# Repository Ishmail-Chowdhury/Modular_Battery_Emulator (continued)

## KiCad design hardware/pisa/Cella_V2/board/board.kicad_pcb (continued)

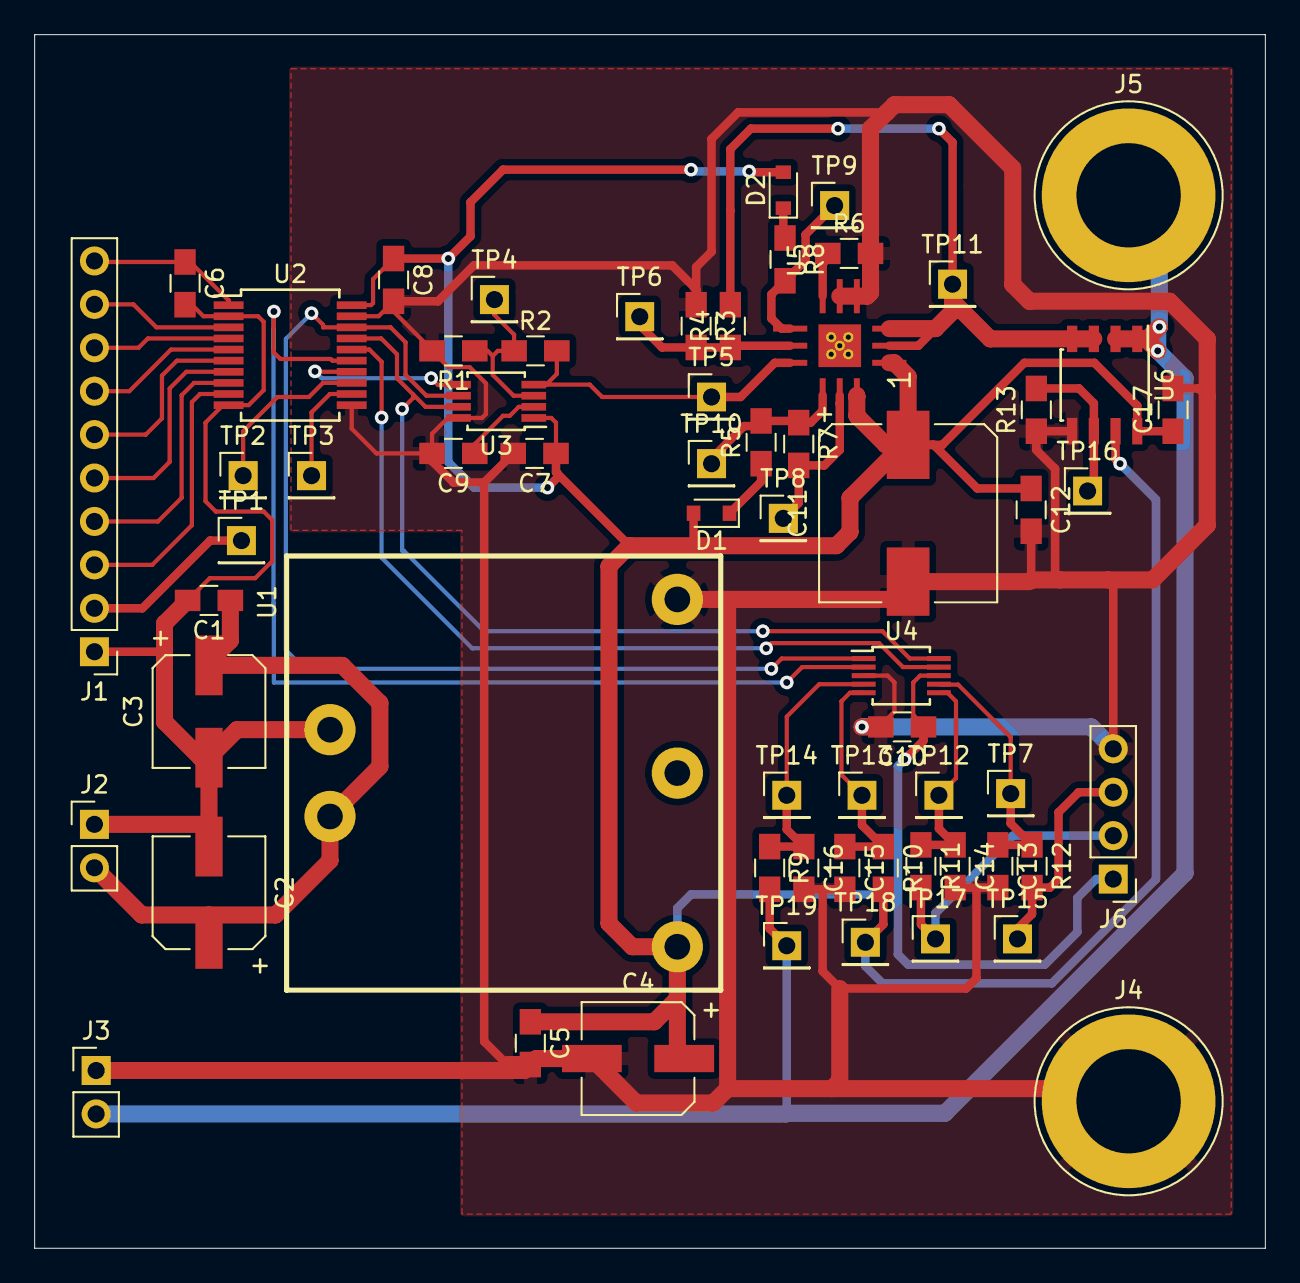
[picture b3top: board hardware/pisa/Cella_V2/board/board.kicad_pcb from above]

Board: 2 copper layers, 72.0 x 71.0 mm, 63 parts (0 on the bottom side), 40 nets.

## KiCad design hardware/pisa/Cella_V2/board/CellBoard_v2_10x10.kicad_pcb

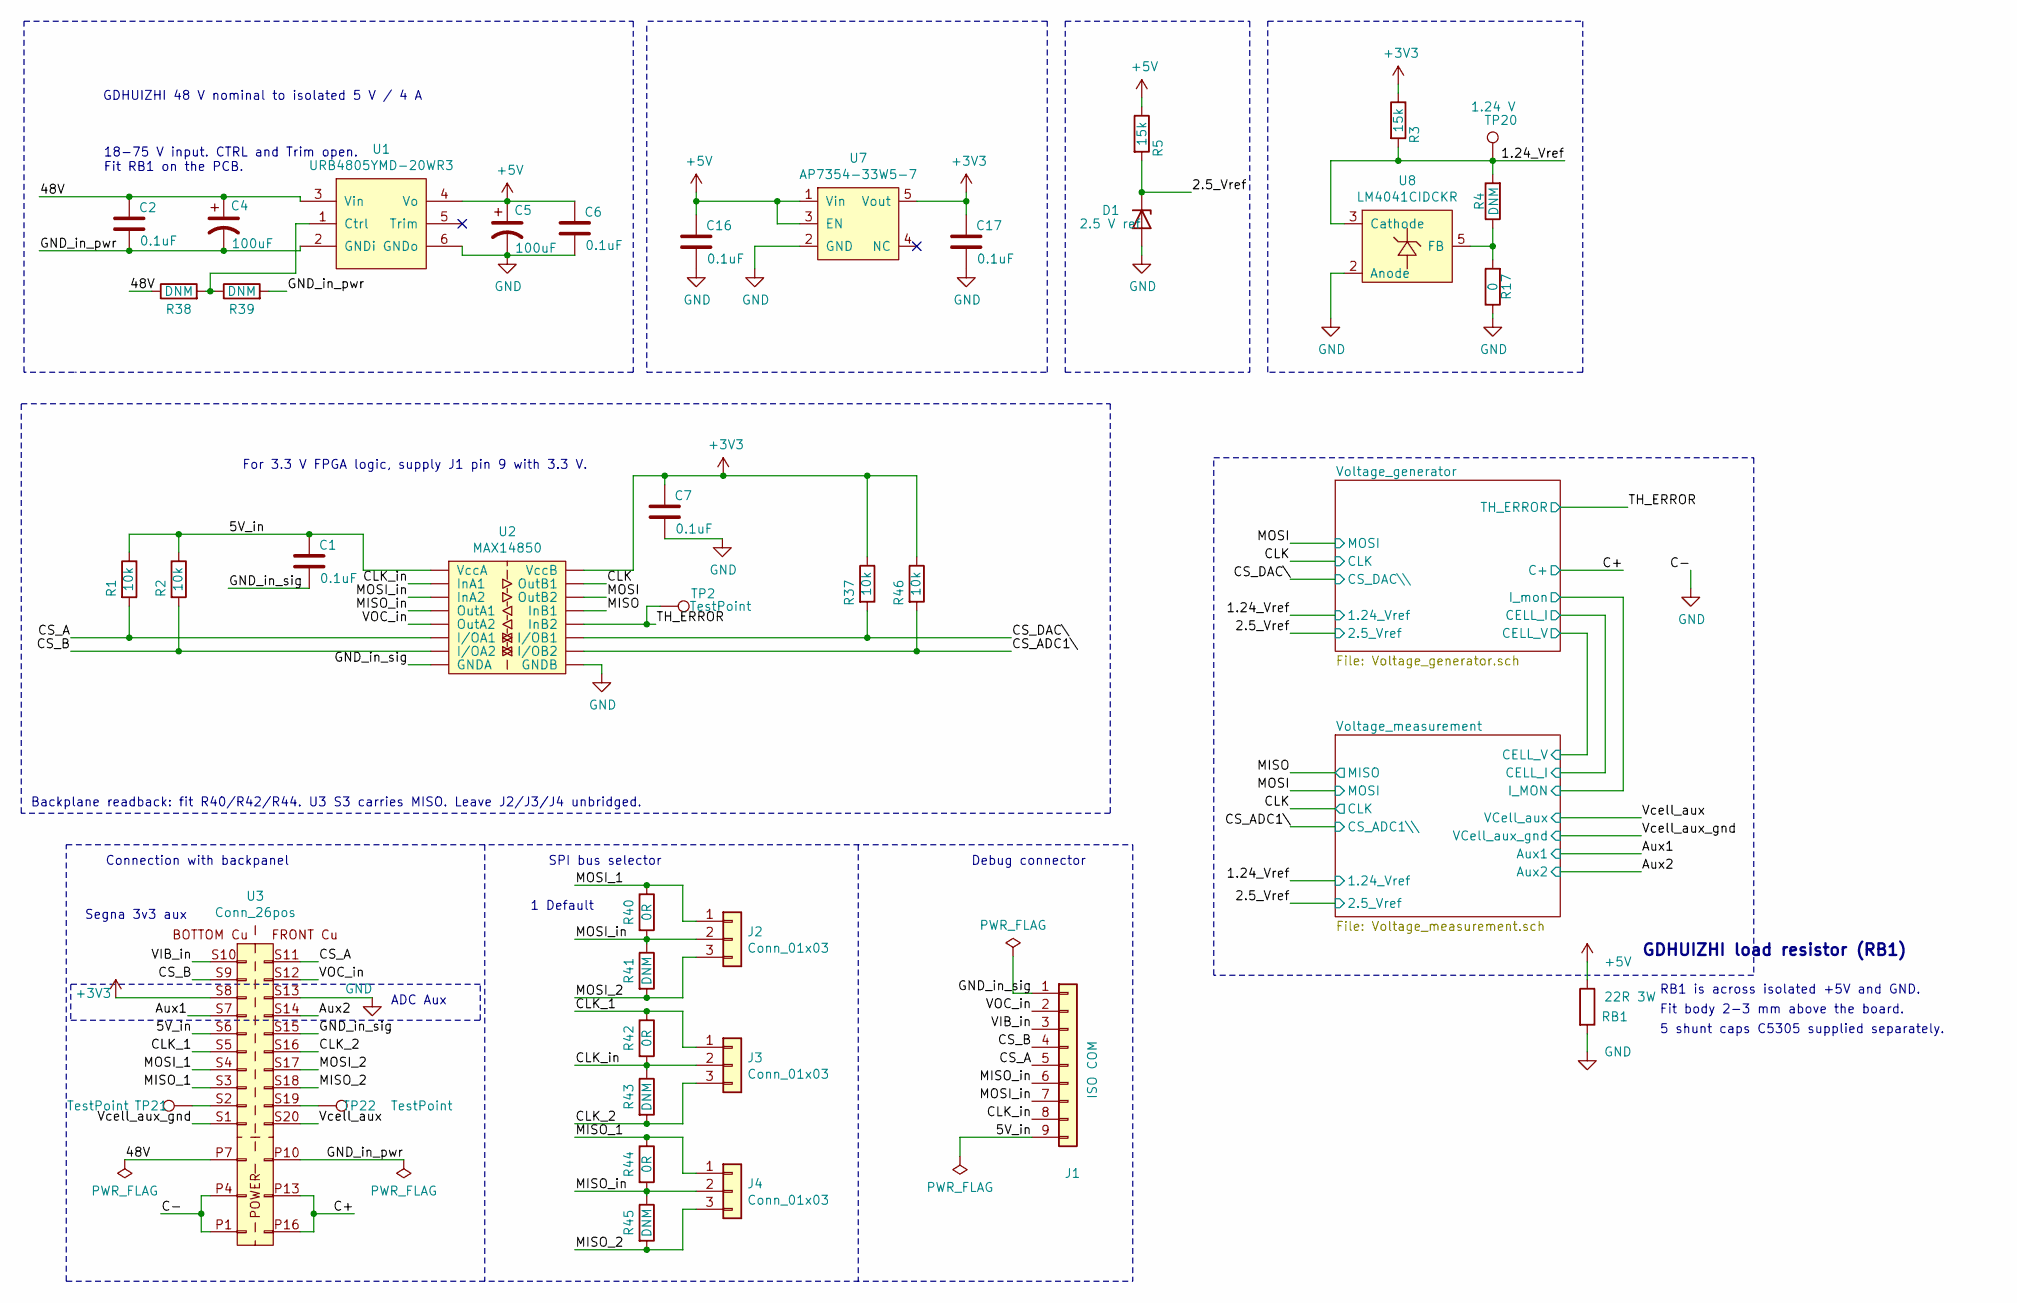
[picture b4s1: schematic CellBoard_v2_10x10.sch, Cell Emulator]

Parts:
C1, C2, C6, C7, C16, C17: 0.1uF; C_0805_2012Metric_Pad1.18x1.45mm_HandSolder; JLCPCB C28233
C4, C5: 100uF; CP_Radial_D10.0mm_P5.00mm; JLCPCB C330940
D1: 2.5 V ref; SOT-23; JLCPCB C2157047
J1: ISO COM; PinHeader_1x09_P2.54mm_Vertical; JLCPCB C2337
J2, J3, J4: Conn_01x03; PinHeader_1x03_P2.54mm_Vertical; JLCPCB C2337
R1, R2, R37, R46: 10k; R_0805_2012Metric_Pad1.20x1.40mm_HandSolder; JLCPCB C110775
R3, R5: 15k; R_0805_2012Metric_Pad1.20x1.40mm_HandSolder; JLCPCB C17475
R4: DNM; R_0805_2012Metric_Pad1.20x1.40mm_HandSolder; Digikey PN RMCF0805ZT0R00CT-ND
R17: 0; R_0805_2012Metric_Pad1.20x1.40mm_HandSolder; JLCPCB C17477
R38, R39: DNM; R_0603_1608Metric_Pad0.98x0.95mm_HandSolder
R40, R42, R44: 0R; R_0402_1005Metric_Pad0.72x0.64mm_HandSolder; JLCPCB C106231
R41, R43, R45: DNM; R_0402_1005Metric_Pad0.72x0.64mm_HandSolder; Digikey PN RMCF0805ZT0R00CT-ND
RB1: 22R 3W; R_Axial_DIN0516_L15.5mm_D5.0mm_P20.32mm_Horizontal; JLCPCB C122827
TP2, TP21, TP22: TestPoint; PinHeader_1x01_P2.54mm_Vertical
TP20: 1.24 V; PinHeader_1x01_P2.54mm_Vertical
U1: URB4805YMD-20WR3; JLCPCB C55020094
U2: MAX14850; SOIC-16_3.9x9.9mm_P1.27mm; JLCPCB C143356
U3: Conn_26pos; Conn_26pos_Board; Digikey PN A107666-ND (Header)
U7: AP7354-33W5-7; TSOT-23-5_HandSoldering; JLCPCB C460386
U8: LM4041CIDCKR; JLCPCB C2156783

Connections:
+3V3: C7.1, C17.1, R3.1, R37.1, R46.1, U2.16 (VccB), U3.S8, U7.5 (Vout); also elsewhere on the board
+5V: C5.1, C6.1, C16.1, R5.1, RB1.1, U1.4 (Vo), U7.1 (Vin), U7.3 (EN); also elsewhere on the board
/1.24_Vref: R3.2, R4.2, TP20.1, U8.3 (Cathode); also elsewhere on the board
/2.5_Vref: D1.1 (K), R5.2; also elsewhere on the board
/5V_in: C1.1, J1.9, R1.1, R2.1, U2.1 (VccA), U3.S6
/48V: C2.1, C4.1, R38.1, U1.3 (Vin), U3.P7
/Aux1: U3.S7; also elsewhere on the board
/Aux2: U3.S14; also elsewhere on the board
/C+: U3.P13, U3.P16; also elsewhere on the board
/CLK: U2.15 (OutB1); also elsewhere on the board
/CLK_1: J3.1, R42.1, U3.S5
/CLK_2: J3.3, R43.2, U3.S16
/CLK_in: J1.8, J3.2, R42.2, R43.1, U2.2 (InA1)
/CS_A: J1.5, R1.2, U2.6 (I/OA1), U3.S11
/CS_ADC1\: R46.2, U2.10 (I/OB2); also elsewhere on the board
/CS_B: J1.4, R2.2, U2.7 (I/OA2), U3.S9
/CS_DAC\: R37.2, U2.11 (I/OB1); also elsewhere on the board
/GND_in_pwr: C2.2, C4.2, R39.2, U1.2 (GNDi), U3.P10
/GND_in_sig: C1.2, J1.1, U2.8 (GNDA), U3.S15
/MISO: U2.13 (InB1); also elsewhere on the board
/MISO_1: J4.1, R44.1, U3.S3
/MISO_2: J4.3, R45.2, U3.S18
/MISO_in: J1.6, J4.2, R44.2, R45.1, U2.4 (OutA1)
/MOSI: U2.14 (OutB2); also elsewhere on the board
/MOSI_1: J2.1, R40.1, U3.S4
/MOSI_2: J2.3, R41.2, U3.S17
/MOSI_in: J1.7, J2.2, R40.2, R41.1, U2.3 (InA2)
/TH_ERROR: TP2.1, U2.12 (InB2); also elsewhere on the board
/VIB_in: J1.3, U3.S10
/VOC_in: J1.2, U2.5 (OutA2), U3.S12
/Vcell_aux: U3.S20; also elsewhere on the board
/Vcell_aux_gnd: U3.S1; also elsewhere on the board
GND: C5.2, C6.2, C7.2, C16.2, C17.2, D1.2 (A), R17.1, RB1.2, U1.6 (GNDo), U2.9 (GNDB), U3.P1, U3.P4, U3.S13, U7.2 (GND), U8.2 (Anode); also elsewhere on the board
unnamed: R4.1, R17.2, U8.5 (FB)
unnamed: R38.2, R39.1, U1.1 (Ctrl)
unnamed: TP21.1, U3.S2
unnamed: TP22.1, U3.S19

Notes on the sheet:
18-75 V input. CTRL and Trim open. Fit RB1 on the PCB.
Connection with backpanel
For 3.3 V FPGA logic, supply J1 pin 9 with 3.3 V.
GDHUIZHI 48 V nominal to isolated 5 V / 4 A
SPI bus selector
Debug connector
1 Default
Segna 3v3 aux
ADC Aux
GDHUIZHI load resistor (RB1)
RB1 is across isolated +5V and GND.
Fit body 2-3 mm above the board.
5 shunt caps C5305 supplied separately.
Backplane readback: fit R40/R42/R44. U3 S3 carries MISO. Leave J2/J3/J4 unbridged.

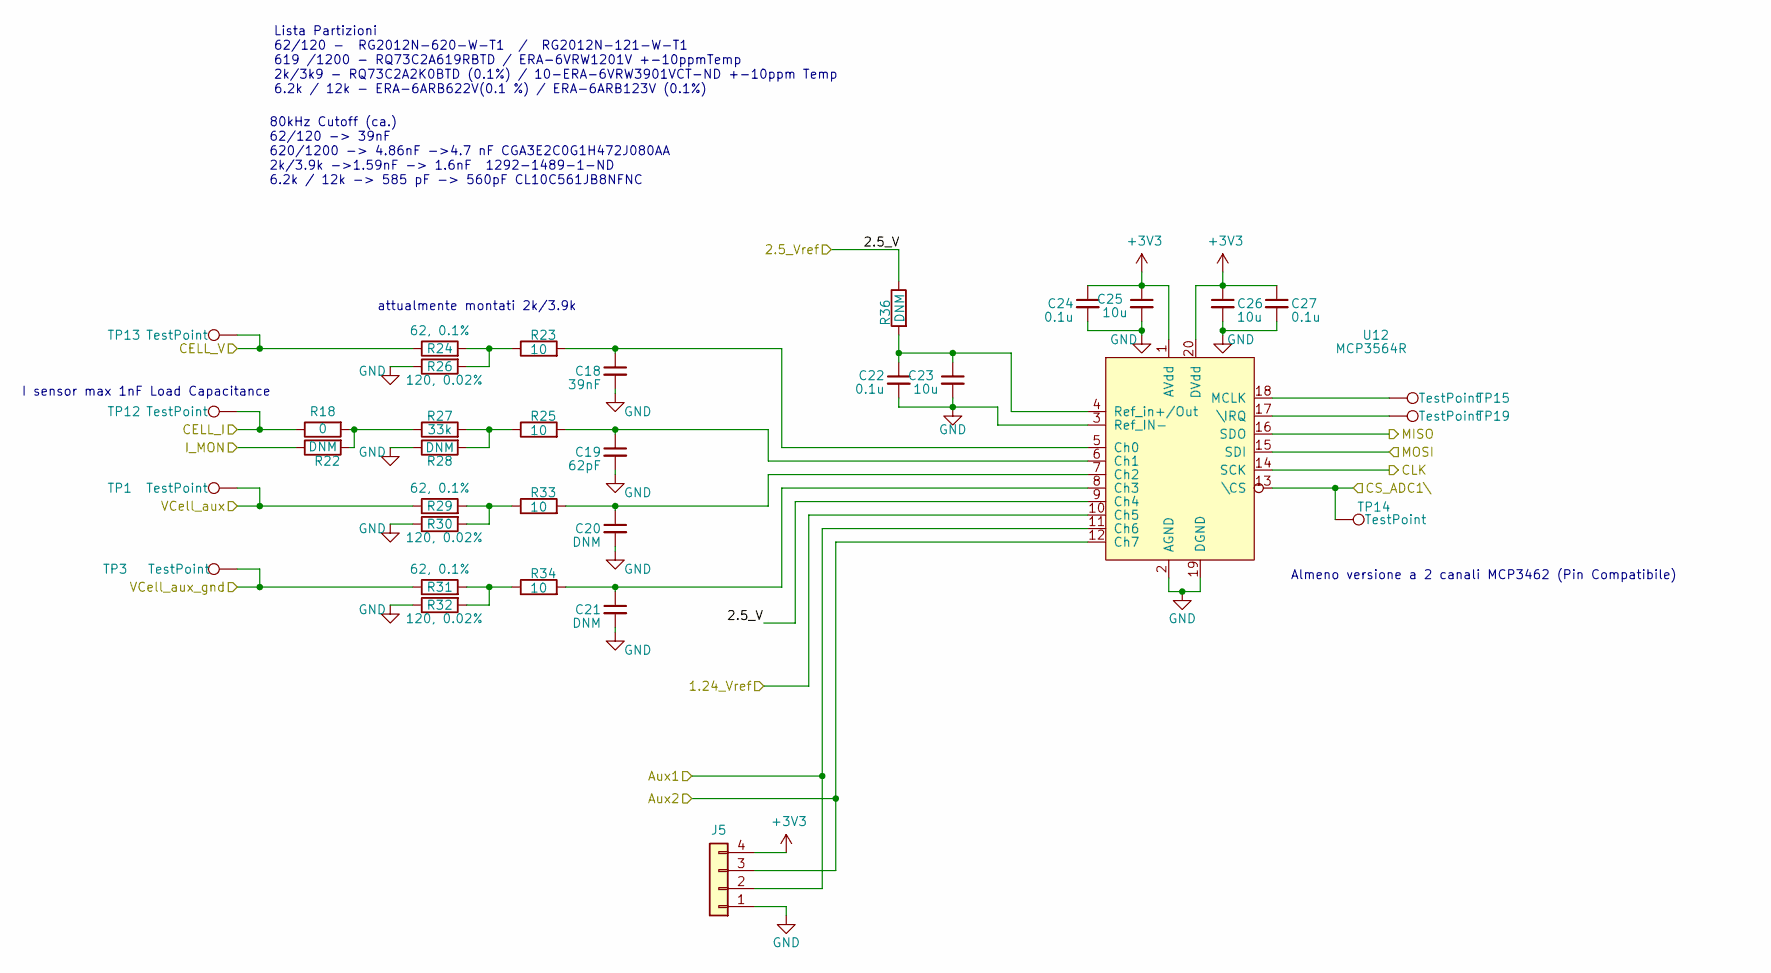
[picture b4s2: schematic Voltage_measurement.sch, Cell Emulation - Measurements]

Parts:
C18: 39nF; C_0603_1608Metric_Pad1.08x0.95mm_HandSolder; JLCPCB C318636
C19: 62pF; C_0603_1608Metric_Pad1.08x0.95mm_HandSolder; JLCPCB C519495
C20, C21: DNM; C_0603_1608Metric_Pad1.08x0.95mm_HandSolder; Digikey PN 1276-2057-1-ND
C22, C24, C27: 0.1u; C_0603_1608Metric_Pad1.08x0.95mm_HandSolder; JLCPCB C1591
C23, C25, C26: 10u; C_0805_2012Metric_Pad1.18x1.45mm_HandSolder; JLCPCB C3039694
J5: Conn_01x04-Connector_Generic; PinHeader_1x04_P2.54mm_Vertical; JLCPCB C2337
R18: 0; R_0805_2012Metric_Pad1.20x1.40mm_HandSolder; JLCPCB C17477
R22, R36: DNM; R_0805_2012Metric_Pad1.20x1.40mm_HandSolder; Digikey PN RMCF0805ZT0R00CT-ND
R23, R25, R33, R34: 10; R_0603_1608Metric_Pad0.98x0.95mm_HandSolder; JLCPCB C3029194
R24, R29, R31: 62, 0.1%; R_0805_2012Metric_Pad1.20x1.40mm_HandSolder; JLCPCB C351555
R26, R30, R32: 120, 0.02%; R_0805_2012Metric_Pad1.20x1.40mm_HandSolder; JLCPCB C19706317
R27: 33k; R_0805_2012Metric_Pad1.20x1.40mm_HandSolder; JLCPCB C17633
R28: DNM; R_0805_2012Metric_Pad1.20x1.40mm_HandSolder
TP1, TP3, TP12, TP13, TP14, TP15, TP19: TestPoint; PinHeader_1x01_P2.54mm_Vertical
U12: MCP3564R; TSSOP-20_4.4x6.5mm_P0.65mm; JLCPCB C5227404

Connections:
+3V3: C24.1, C25.1, C26.1, C27.1, J5.4, U12.1 (AVdd), U12.20 (DVdd); also elsewhere on the board
/1.24_Vref: U12.10 (Ch5); also elsewhere on the board
/2.5_Vref: R36.1, U12.9 (Ch4); also elsewhere on the board
/Aux1: J5.2, U12.11 (Ch6); also elsewhere on the board
/Aux2: J5.3, U12.12 (Ch7); also elsewhere on the board
/C+: R24.1, TP13.1; also elsewhere on the board
/CLK: U12.14 (SCK); also elsewhere on the board
/CS_ADC1\: TP14.1, U12.13 (\CS); also elsewhere on the board
/MISO: U12.16 (SDO); also elsewhere on the board
/MOSI: U12.15 (SDI); also elsewhere on the board
/Vcell_aux: R29.1, TP1.1; also elsewhere on the board
/Vcell_aux_gnd: R31.1, TP3.1; also elsewhere on the board
/Voltage_generator/CELL_I: R18.1, TP12.1; also elsewhere on the board
/Voltage_measurement/I_MON: R22.1; also elsewhere on the board
GND: C18.2, C19.2, C20.2, C21.2, C22.2, C23.2, C24.2, C25.2, C26.2, C27.2, J5.1, R26.1, R28.1, R30.1, R32.1, U12.2 (AGND), U12.3 (Ref_IN-), U12.19 (DGND); also elsewhere on the board
unnamed: C18.1, R23.2, U12.5 (Ch0)
unnamed: C19.1, R25.2, U12.6 (Ch1)
unnamed: C20.1, R33.2, U12.7 (Ch2)
unnamed: C21.1, R34.2, U12.8 (Ch3)
unnamed: C22.1, C23.1, R36.2, U12.4 (Ref_in+/Out)
unnamed: R18.2, R22.2, R27.1
unnamed: R23.1, R24.2, R26.2
unnamed: R25.1, R27.2, R28.2
unnamed: R29.2, R30.2, R33.1
unnamed: R31.2, R32.2, R34.1
unnamed: TP15.1, U12.18 (MCLK)
unnamed: TP19.1, U12.17 (\IRQ)

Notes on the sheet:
Lista Partizioni 62/120 - RG2012N-620-W-T1 / RG2012N-121-W-T1 619 /1200 - RQ73C2A619RBTD / ERA-6VRW1201V +-10ppmTemp 2k/3k9 - RQ73C2A2K0BTD (0.1%) / 10-ERA-6VRW3901VCT-ND +-10ppm Temp 6.2k / 12k - ERA-6ARB622V(0.1 %) / ERA-6ARB123V (0.1%)
I sensor max 1nF Load Capacitance
80kHz Cutoff (ca.) 62/120 -> 39nF 620/1200 -> 4.86nF ->4.7 nF CGA3E2C0G1H472J080AA 2k/3.9k ->1.59nF -> 1.6nF 1292-1489-1-ND 6.2k / 12k -> 585 pF -> 560pF CL10C561JB8NFNC
Almeno versione a 2 canali MCP3462 (Pin Compatibile)
attualmente montati 2k/3.9k

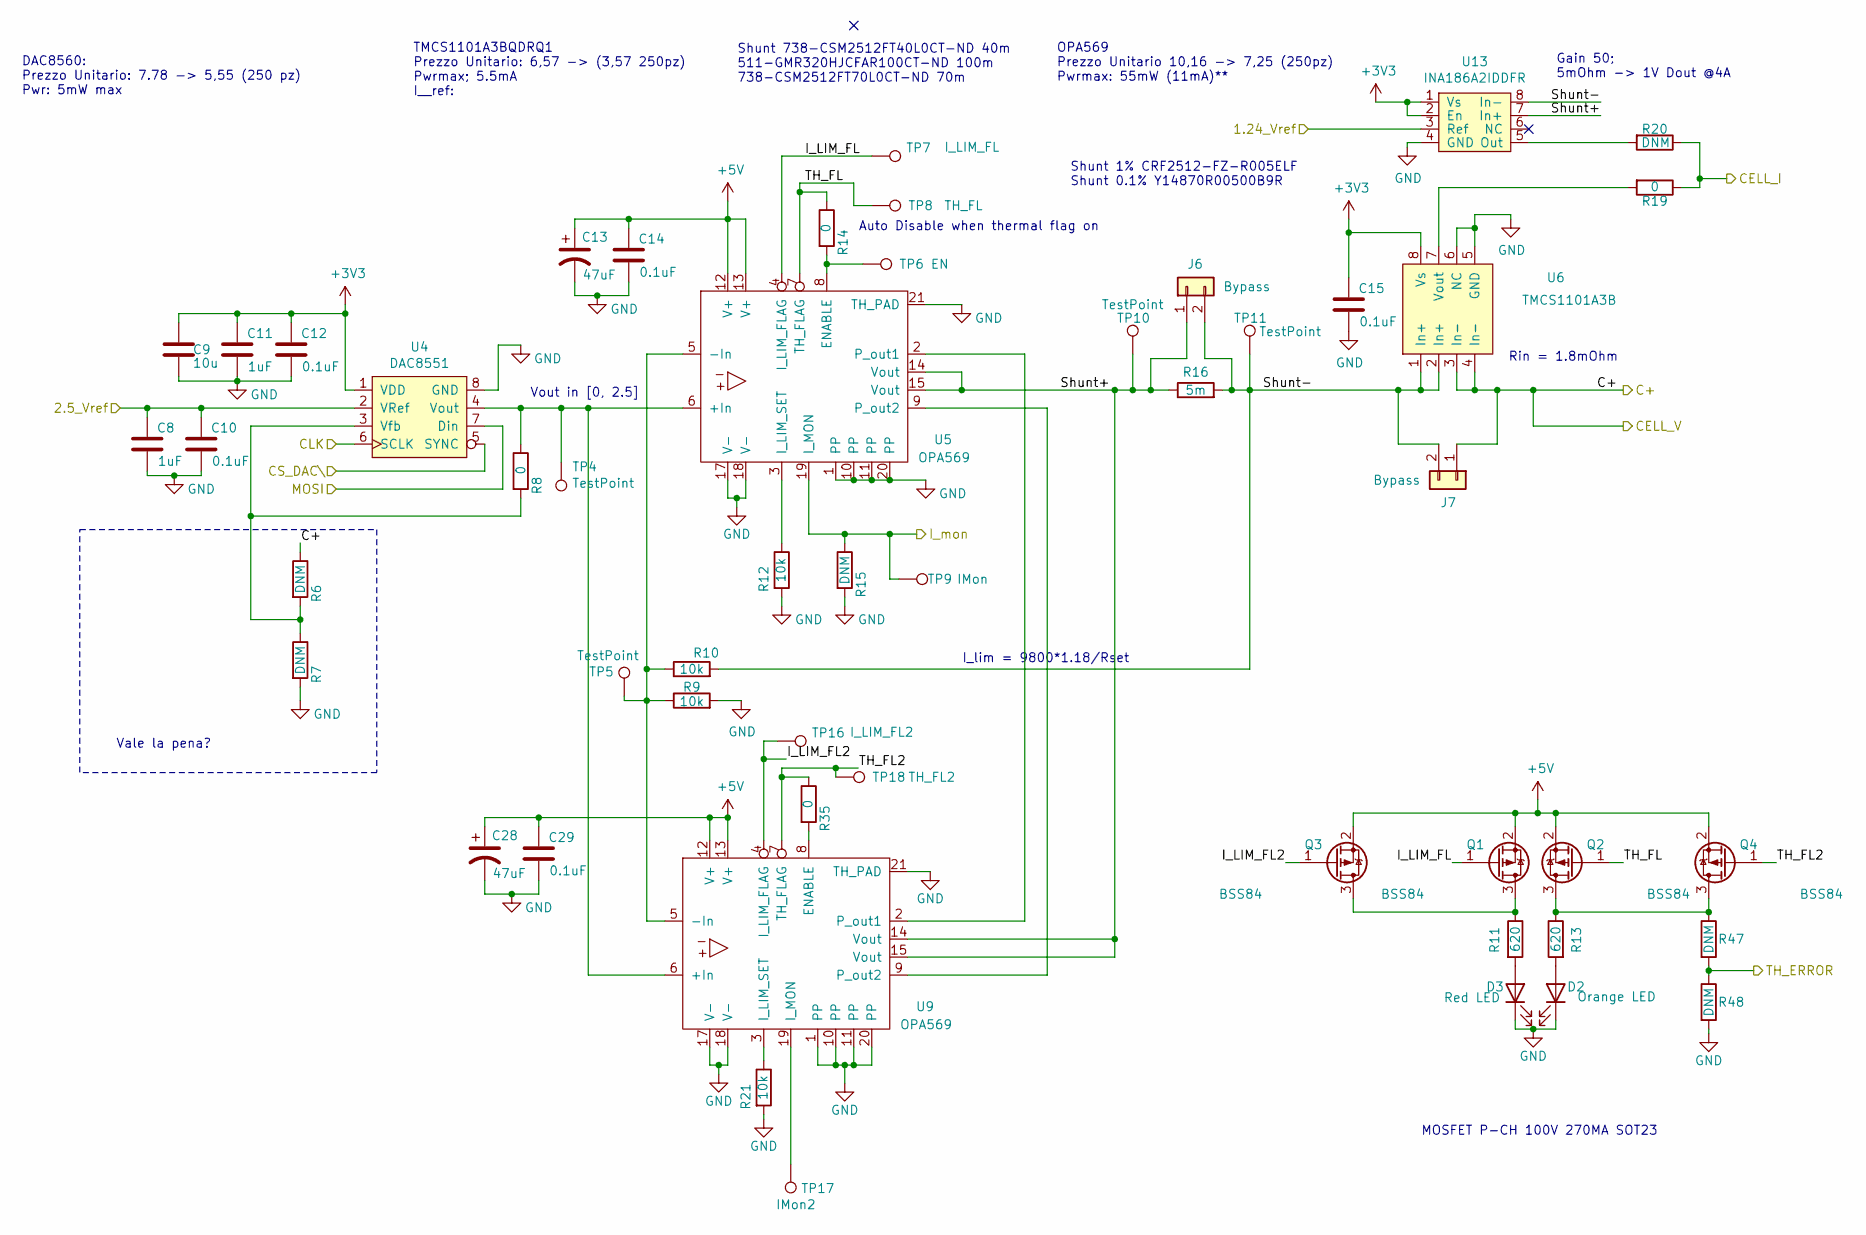
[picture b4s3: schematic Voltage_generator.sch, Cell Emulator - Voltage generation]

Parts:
C8, C11: 1uF; C_0805_2012Metric_Pad1.18x1.45mm_HandSolder; JLCPCB C28323
C9: 10u; C_0805_2012Metric_Pad1.18x1.45mm_HandSolder; JLCPCB C3039694
C10, C12, C14, C15, C29: 0.1uF; C_0805_2012Metric_Pad1.18x1.45mm_HandSolder; JLCPCB C28233
C13, C28: 47uF; CP_EIA-7343-31_Kemet-D_Pad2.25x2.55mm_HandSolder; JLCPCB C127511
D2: Orange LED; D_0805_2012Metric_Pad1.15x1.40mm_HandSolder; JLCPCB C284931
D3: Red LED; D_0805_2012Metric_Pad1.15x1.40mm_HandSolder; JLCPCB C94868
J6, J7: Bypass; PinHeader_1x02_P2.54mm_Vertical; JLCPCB C2337
Q1, Q2, Q3, Q4: BSS84; SOT-23; JLCPCB C493579
R6, R7: DNM; R_0805_2012Metric_Pad1.20x1.40mm_HandSolder; Digikey PN YAG1763CT-ND
R8, R14, R19, R35: 0; R_0805_2012Metric_Pad1.20x1.40mm_HandSolder; JLCPCB C17477
R9, R10, R12, R21: 10k; R_0805_2012Metric_Pad1.20x1.40mm_HandSolder; JLCPCB C110775
R11, R13: 620; R_0603_1608Metric_Pad0.98x0.95mm_HandSolder; JLCPCB C23220
R15, R47, R48: DNM; R_0603_1608Metric_Pad0.98x0.95mm_HandSolder; Digikey PN RMCF0805ZT0R00CT-ND
R16: 5m; Shunt; JLCPCB C2089602
R20: DNM; R_0805_2012Metric_Pad1.20x1.40mm_HandSolder; Digikey PN RMCF0805ZT0R00CT-ND
TP4, TP5, TP10, TP11: TestPoint; PinHeader_1x01_P2.54mm_Vertical
TP6: EN; PinHeader_1x01_P2.54mm_Vertical
TP7: I_LIM_FL; PinHeader_1x01_P2.54mm_Vertical
TP8: TH_FL; PinHeader_1x01_P2.54mm_Vertical
TP9: IMon; PinHeader_1x01_P2.54mm_Vertical
TP16: I_LIM_FL2; PinHeader_1x01_P2.54mm_Vertical
TP17: IMon2; PinHeader_1x01_P2.54mm_Vertical
TP18: TH_FL2; PinHeader_1x01_P2.54mm_Vertical
U4: DAC8551; VSSOP-8_3.0x3.0mm_P0.65mm; JLCPCB C477934
U5, U9: OPA569; OPA569AIDWP; JLCPCB C529573
U6: TMCS1101A3B; TMCS1101_D0008B; JLCPCB C2871609
U13: INA186A2IDDFR; SOT-23-8_Handsoldering; JLCPCB C2869854

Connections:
+3V3: C9.1, C11.1, C12.1, C15.1, U4.1 (VDD), U6.8 (Vs), U13.1 (Vs), U13.2 (En); also elsewhere on the board
+5V: C13.1, C14.1, C28.1, C29.1, Q1.2 (S), Q2.2 (S), Q3.2 (S), Q4.2 (S), U5.12 (V+), U5.13 (V+), U9.12 (V+), U9.13 (V+); also elsewhere on the board
/1.24_Vref: U13.3 (Ref); also elsewhere on the board
/2.5_Vref: C8.1, C10.1, U4.2 (VRef); also elsewhere on the board
/C+: J7.1, R6.1, U6.3 (In-), U6.4 (In-); also elsewhere on the board
/CLK: U4.6 (SCLK); also elsewhere on the board
/CS_DAC\: U4.5 (SYNC); also elsewhere on the board
/MOSI: U4.7 (Din); also elsewhere on the board
/TH_ERROR: R47.2, R48.1; also elsewhere on the board
/Voltage_generator/CELL_I: R19.1, R20.1; also elsewhere on the board
/Voltage_generator/I_LIM_FL: Q1.1 (G), TP7.1, U5.4 (I_LIM_FLAG)
/Voltage_generator/I_LIM_FL2: Q3.1 (G), TP16.1, U9.4 (I_LIM_FLAG)
/Voltage_generator/Shunt+: J6.1, R16.1, TP10.1, U5.14 (Vout), U5.15 (Vout), U9.14 (Vout), U9.15 (Vout), U13.7 (In+)
/Voltage_generator/Shunt-: J6.2, J7.2, R10.2, R16.2, TP11.1, U6.1 (In+), U6.2 (In+), U13.8 (In-)
/Voltage_generator/TH_FL: Q2.1 (G), R14.1, TP8.1, U5.7 (TH_FLAG)
/Voltage_generator/TH_FL2: Q4.1 (G), R35.1, TP18.1, U9.7 (TH_FLAG)
/Voltage_measurement/I_MON: R15.1, TP9.1, U5.19 (I_MON); also elsewhere on the board
GND: C8.2, C9.2, C10.2, C11.2, C12.2, C13.2, C14.2, C15.2, C28.2, C29.2, D2.1 (K), D3.1 (K), R7.2, R9.2, R12.2, R15.2, R21.2, R48.2, U4.8 (GND), U5.1 (PP), U5.10 (PP), U5.11 (PP), U5.17 (V-), U5.18 (V-), U5.20 (PP), U5.21 (TH_PAD), U6.5 (GND), U6.6 (NC), U9.1 (PP), U9.10 (PP), U9.11 (PP), U9.17 (V-), U9.18 (V-), U9.20 (PP), U9.21 (TH_PAD), U13.4 (GND); also elsewhere on the board
unnamed: D2.2 (A), R13.2
unnamed: D3.2 (A), R11.2
unnamed: Q1.3 (D), Q3.3 (D), R11.1
unnamed: Q2.3 (D), Q4.3 (D), R13.1, R47.1
unnamed: R6.2, R7.1, R8.2, U4.3 (Vfb)
unnamed: R8.1, TP4.1, U4.4 (Vout), U5.6 (+In), U9.6 (+In)
unnamed: R9.1, R10.1, TP5.1, U5.5 (-In), U9.5 (-In)
unnamed: R12.1, U5.3 (I_LIM_SET)
unnamed: R14.2, TP6.1, U5.8 (ENABLE)
unnamed: R19.2, U6.7 (Vout)
unnamed: R20.2, U13.5 (Out)
unnamed: R21.1, U9.3 (I_LIM_SET)
unnamed: R35.2, U9.8 (ENABLE)
unnamed: TP17.1, U9.19 (I_MON)
unnamed: U5.2 (P_out1), U9.2 (P_out1)
unnamed: U5.9 (P_out2), U9.9 (P_out2)

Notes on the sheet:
DAC8560: Prezzo Unitario: 7.78 -> 5,55 (250 pz) Pwr: 5mW max
OPA569 Prezzo Unitario 10,16 -> 7,25 (250pz) Pwrmax: 55mW (11mA)**
TMCS1101A3BQDRQ1 Prezzo Unitario: 6,57 -> (3,57 250pz) Pwrmax; 5.5mA I__ref:
Vout in [0, 2.5]
Auto Disable when thermal flag on
I_lim = 9800*1.18/Rset
Vale la pena?
MOSFET P-CH 100V 270MA SOT23
Shunt 738-CSM2512FT40L0CT-ND 40m 511-GMR320HJCFAR100CT-ND 100m 738-CSM2512FT70L0CT-ND 70m
Rin = 1.8mOhm
Gain 50; 5mOhm -> 1V Dout @4A
Shunt 1% CRF2512-FZ-R005ELF Shunt 0.1% Y14870R00500B9R

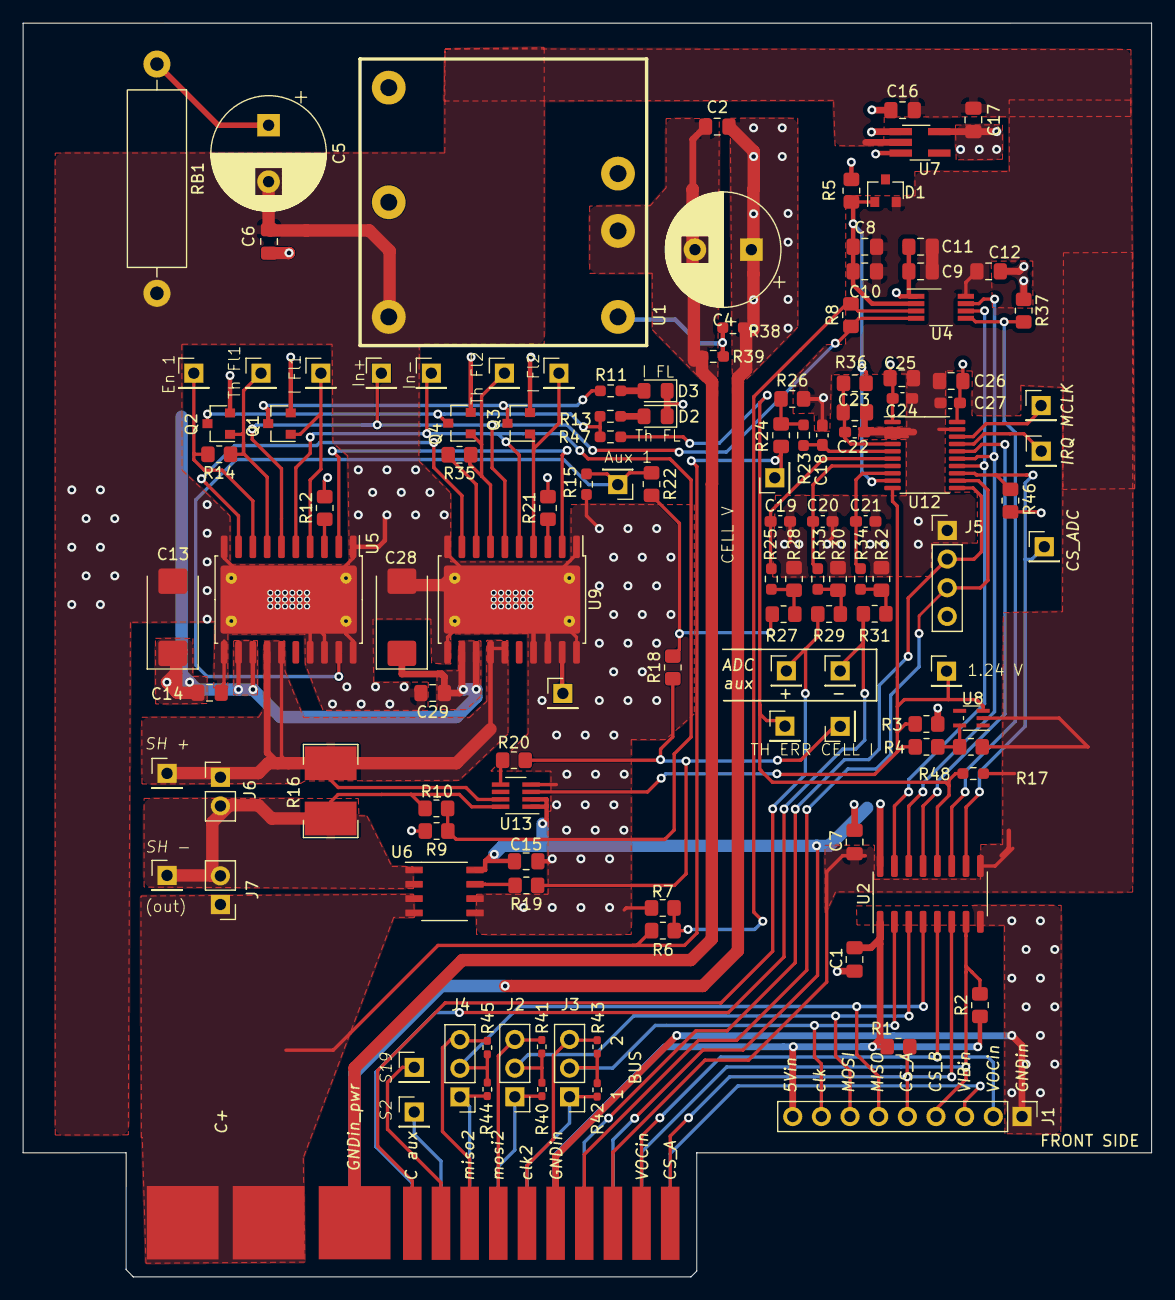
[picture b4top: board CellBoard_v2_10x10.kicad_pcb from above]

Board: 2 copper layers, 100.0 x 111.1 mm, 124 parts (0 on the bottom side), 73 nets.

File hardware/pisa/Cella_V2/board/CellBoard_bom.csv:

Reference; Quantity; Value; Footprint; Datasheet; Descrizione; Digikey PN; Manufacturer; PN;Colonna1; Man; Digikey Mating; Mating
C8 C11 ;2;1uF;Capacitor_SMD:C_0805_2012Metric_Pad1.18x1.45mm_HandSolder;~;;1276-6471-1-ND;Samsung Electro-Mechanics;CL21B105KOFNNNG;;;;
C13 C28 ;2;47uF;Capacitor_Tantalum_SMD:CP_EIA-7343-31_Kemet-D_Pad2.25x2.55mm_HandSolder;~;;478-3936-1-ND;KYOCERA AVX;TAJD476K020RNJ;;;;
C18 ;4;39nF;Capacitor_SMD:C_0603_1608Metric_Pad1.08x0.95mm_HandSolder;~;;1276-2057-1-ND;Samsung Electro-Mechanics;CL10B393KO8NNNC;;;;
C19 ;1;62pF;Capacitor_SMD:C_0603_1608Metric_Pad1.08x0.95mm_HandSolder;~;;478-10243-1-ND;KYOCERA AVX;06031U620FAT2A;;;;
C20 C21 ;2;DNM;Capacitor_SMD:C_0603_1608Metric_Pad1.08x0.95mm_HandSolder;~;;1276-2057-1-ND;Samsung Electro-Mechanics;CL10B393KO8NNNC;;;;
C9 C23 C25 C26 ;4;10u;Capacitor_SMD:C_0805_2012Metric_Pad1.18x1.45mm_HandSolder;~;;1276-6472-1-ND;Samsung Electro-Mechanics;CL21B106KOQNNNG;;;;
C22 C24 C27 ;3;0.1u;Capacitor_SMD:C_0603_1608Metric_Pad1.08x0.95mm_HandSolder;~;;1276-CL10B104KB8NNNLCT-ND;Samsung Electro-Mechanics;CL10B104KB8NNNL;;;;
C4 C5 ;2;100uF;Capacitor_THT:CP_Radial_D10.0mm_P5.00mm;~;;399-ESH107M100AH4AA-ND;KEMET;ESH107M100AH4AA;;;;
C1 C2 C6 C7 C10 C12 C14 C15 C16 C17 C29 ;11;0.1uF;Capacitor_SMD:C_0805_2012Metric_Pad1.18x1.45mm_HandSolder;~;;1276-6840-1-ND;Samsung Electro-Mechanics;CL21B104KCFNNNE;;;;
D1 ;1;2.5 Ref;Package_TO_SOT_SMD:SOT-23;~;;296-22783-1-ND;Texas Instruments;TL4050A25IDBZR;;;;
D2 ;1;ORANGE LED;Diode_SMD:D_0805_2012Metric_Pad1.15x1.40mm_HandSolder;~;;475-2488-1-ND;OSRAM Opto Semiconductors Inc.;LO R976-PS-1;;;;
D3 ;1;RED LED;Diode_SMD:D_0805_2012Metric_Pad1.15x1.40mm_HandSolder;~;;475-1278-1-ND;OSRAM Opto Semiconductors Inc.;LS R976-NR-1;;;;
J1 ;1;ISO COM;Connector_PinHeader_2.54mm:PinHeader_1x09_P2.54mm_Vertical;~;;;;;;;;
J2 J3 J4 ;3;Conn_01x03;Connector_PinHeader_2.54mm:PinHeader_1x03_P2.54mm_Vertical;~;;;;;;;;
J5 ;1;Conn_01x04-Connector_Generic;Connector_PinHeader_2.54mm:PinHeader_1x04_P2.54mm_Vertical;;;;;;;;;
J6 J7 ;2;Bypass;Connector_PinHeader_2.54mm:PinHeader_1x02_P2.54mm_Vertical;;;SAM9159-ND;Samtec Inc.;TMM-102-02-L-S;;;SAM8748-ND;2SN-BK-G
Q1 Q2 Q3 Q4 ;4;DMP10H4D2S-7;Package_TO_SOT_SMD:SOT-23;~;;DMP10H4D2S-7DICT-ND;Diodes Incorporated;DMP10H4D2S-7;;;;
R11 R13 ;2;620;Resistor_SMD:R_0603_1608Metric_Pad0.98x0.95mm_HandSolder;~;;RMCF0603JT620RCT-ND;Stackpole Electronics Inc;RMCF0603JT620R;;;;
R6 R7 R9 R10 R12 R21 ;6;10k;Resistor_SMD:R_0805_2012Metric_Pad1.20x1.40mm_HandSolder;~;;YAG1763CT-ND;YAGEO;RT0805BRD0710KL;;;;
R16 ;1;5m;board:Shunt;~;;CRF2512-FZ-R005ELFCT-ND;Bourns Inc.;CRF2512-FZ-R005ELF;;;;
R17 R28;2;DNM;Resistor_SMD:R_0805_2012Metric_Pad1.20x1.40mm_HandSolder;~;;;;;;;;
R23 R25 R33 R34 ;4;10;Resistor_SMD:R_0603_1608Metric_Pad0.98x0.95mm_HandSolder;~;;RMCF0603FT10R0CT-ND;Stackpole Electronics Inc;RMCF0603FT10R0;;;;
R24 R29 R31 ;3;62, 0.05%;Resistor_SMD:R_0805_2012Metric_Pad1.20x1.40mm_HandSolder;~;;RG20N62WCT-ND;Susumu;RG2012N-620-W-T1;;;;
R26 R30 R32 ;3;120, 0.05%;Resistor_SMD:R_0805_2012Metric_Pad1.20x1.40mm_HandSolder;~;;RG20N120WCT-ND;Susumu;RG2012N-121-W-T1;;;;
R27 ;1;33k;Resistor_SMD:R_0805_2012Metric_Pad1.20x1.40mm_HandSolder;~;;A129767CT-ND;TE Connectivity Passive Product;CRGCQ0805F33K;;;;
R3 R5 ;2;15k;Resistor_SMD:R_0805_2012Metric_Pad1.20x1.40mm_HandSolder;~;;A126341CT-ND;TE Connectivity Passive Product;CRG0805F15K;;;;
R15 R38 R39 ;3;DNM;Resistor_SMD:R_0603_1608Metric_Pad0.98x0.95mm_HandSolder;~;;;;;;;;
R4 R8 R14 R18 R19 R20 R22 R35 R36;9;0;Resistor_SMD:R_0805_2012Metric_Pad1.20x1.40mm_HandSolder;~;;RMCF0805ZT0R00CT-ND;Stackpole Electronics Inc;RMCF0805ZT0R00;;;;
R40 R41 R42 R43 R44 R45 ;6;DNM;Resistor_SMD:R_0402_1005Metric_Pad0.72x0.64mm_HandSolder;~;;RMCF0805ZT0R00CT-ND;Stackpole Electronics Inc;RMCF0805ZT0R00;;;;
TP16 ;1;I_LIM_FL2;Connector_PinHeader_2.54mm:PinHeader_1x01_P2.54mm_Vertical;~;;;;;;;;
TP17 ;1;IMon2;Connector_PinHeader_2.54mm:PinHeader_1x01_P2.54mm_Vertical;~;;;;;;;;
TP18 ;1;TH_FL2;Connector_PinHeader_2.54mm:PinHeader_1x01_P2.54mm_Vertical;~;;;;;;;;
TP1 TP2 TP3 TP4 TP5 TP10 TP11 TP12 TP13 TP14 TP15 TP19 TP21 TP22 TP23 ;15;TestPoint;Connector_PinHeader_2.54mm:PinHeader_1x01_P2.54mm_Vertical;~;;;;;;;;
TP20 ;1;1.24 V;Connector_PinHeader_2.54mm:PinHeader_1x01_P2.54mm_Vertical;~;;;;;;;;
TP6 ;1;EN;Connector_PinHeader_2.54mm:PinHeader_1x01_P2.54mm_Vertical;~;;;;;;;;
TP7 ;1;I_LIM_FL;Connector_PinHeader_2.54mm:PinHeader_1x01_P2.54mm_Vertical;~;;;;;;;;
TP8 ;1;TH_FL;Connector_PinHeader_2.54mm:PinHeader_1x01_P2.54mm_Vertical;~;;;;;;;;
TP9 ;1;IMon;Connector_PinHeader_2.54mm:PinHeader_1x01_P2.54mm_Vertical;~;;;;;;;;
U1 ;1;URB4805YMD-20WR3;board:URB4805YMD-20WR3;;;2725-URB4805YMD-20WR3-ND;Mornsun America, LLC;URB4805YMD-20WR3;;;;
U10 ;1;LogoUnipi;board:logo_cherubino;;;;;;;;;
U11 ;1;LogoSemes;board:logo_semeslab;;;;;;;;;
U12 ;1;MCP3464R;Package_SO:TSSOP-20_4.4x6.5mm_P0.65mm;;;150-MCP3464RT-E/STCT-ND;Microchip Technology;MCP3464RT-E/ST;;;;
U13 ;1;INA186A2IDDFR;Package_TO_SOT_SMD:SOT-23-8_Handsoldering;;;296-INA186A2IDDFRCT-ND;Texas Instruments;INA186A2IDDFR;;;;
U14 ;1;LogoDII;loghi:logo_dii;;;;;;;;;
U2 ;1;ADUM4151;Package_SO:SOIC-20W_7.5x12.8mm_P1.27mm;;;ADUM4151BRIZ-ND;Analog Devices Inc.;ADUM4151BRIZ;;Analog Devices Inc.;;
U3 ;1;Conn_26pos;board:Conn_26pos_Board;;;A107666-ND (Header);TE Connectivity ;1761426-3 (Header);;;;
U4 ;1;DAC8501;Package_SO:VSSOP-8_3.0x3.0mm_P0.65mm;;;296-DAC8501E/2K5CT-ND;Texas Instruments;DAC8501E/2K5;;;;
U6 ;1;TMCS1101A3BQDRQ1;Package_SO:SOIC-8_5.275x5.275mm_P1.27mm;;;296-TMCS1101A3BQDRQ1CT-ND;Texas Instruments;TMCS1101A3BQDRQ1;; 3;"90mm di larghezza)""";
U7 ;1;AP7354-33W5-7;Package_TO_SOT_SMD:TSOT-23-5_HandSoldering;;;AP7354-33W5-7DICT-ND;Diodes Incorporated;AP7354-33W5-7;;;;
U8 ;1;LM4041CIDCKT;board:LM4041CIDCKR;;;296-32130-1-ND;Texas Instruments;LM4041CIDCKT;;;;
U5 U9 ;2;OPA569;board:OPA569AIDWP;;;296-14174-5-ND;Texas Instruments;OPA569AIDWP;;;;
JUMPER;3;Jumper;;;;SAM8748-ND;Samtec Inc.;2SN-BK-G;;;;
Resistor 60;4;Resistor 60;;;;RG2012N-620-W-T1;;;;;;
Resistor 120;4;Resistor 120;;;;RG2012N-121-W-T1;;;;;;
Resistor 620;4;Resistor 620;;;;RQ73C2A619RBTD ;;;;;;
Resistor 1200;4;Resistor 1200;;;;ERA-6VRW1201V;;;;;;
Resistor 2k;4;Resistor 2k;;;;RQ73C2A2K0BTD;;;;;;
Resistor3k9;4;Resistor3k9;;;;10-ERA-6VRW3901VCT-ND;;;;;;
Resistor 6k2;4;Resistor 6k2;;;;ERA-6ARB622V;;;;;;
Resistor 12k;4;Resistor 12k;;;; ERA-6ARB123V;;;;;;
C4.7n;4;;;;;CGA3E2C0G1H472J080AA;;;;;;
C1.5n;4;;;;;1292-1489-1-ND;;;;;;
560p;4;;;;;CL10C561JB8NFNC;;;;;;
CONN Celle e Cor;9;1761426-3;;;;A107666-ND;TE Connectivity AMP Connectors;1761426-3;;;;
Board Signal Sw out & Tout;5;691402910008B;;;;732-691402910008B-ND;Würth Elektronik;691402910008B;;;;
C out & Curr Out % Power in;10;691137710002;;;;732-10955-ND;Würth Elektronik;691137710002;;;;
Master Conn;1;2-5530843-0;;;;A101955-ND;TE Connectivity AMP Connectors;2-5530843-0;;;;
Temp Conn;1;5-5530843-3;;;;A101974-ND;TE Connectivity AMP Connectors;5-5530843-3;;;;
SSR RELAY SPST-NO 1.25A 0-80V;4;AB47S;;;;1835-1218-ND;Comus International;AB47S;;;;
Backplate R12,R10,R9,R16,R14,R19,R17,R13;8;0;Resistor_SMD:R_0805_2012Metric_Pad1.20x1.40mm_HandSolder;~;;RMCF0805ZT0R00CT-ND;Stackpole Electronics Inc;RMCF0805ZT0R00;RES 0 OHM JUMPER 1/8W 0805;;;
